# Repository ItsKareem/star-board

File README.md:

# A star-shaped blinky board ݁˖ .☆

An LED chaser PCB that uses a NE555 timer (astable mode) and a CD4017 decade counter. I designed the PCB in the shape of a star and added custom silkscreen art to make it more personal. This makes a really cute desk toy and just a fun/beginner-friendly elecronics project. 

## Features
- LED chasing animation with 10 LEDs
- Animation speed can be adjusted using a potentiometer
- Custom star-shaped PCB outline
- Silkscreen art made by me
- THT components

Basically, the 555 generates clock pulses which fed into the CD4017, which sequentially activates each LED, creating the chasing animation.

I made this project as a qualifying project for [fallout](https://www.fallout.hackclub.com), a hardware hackathon organized by hack club Shenzhen, China.

### Front:

### Back:

### PCB:

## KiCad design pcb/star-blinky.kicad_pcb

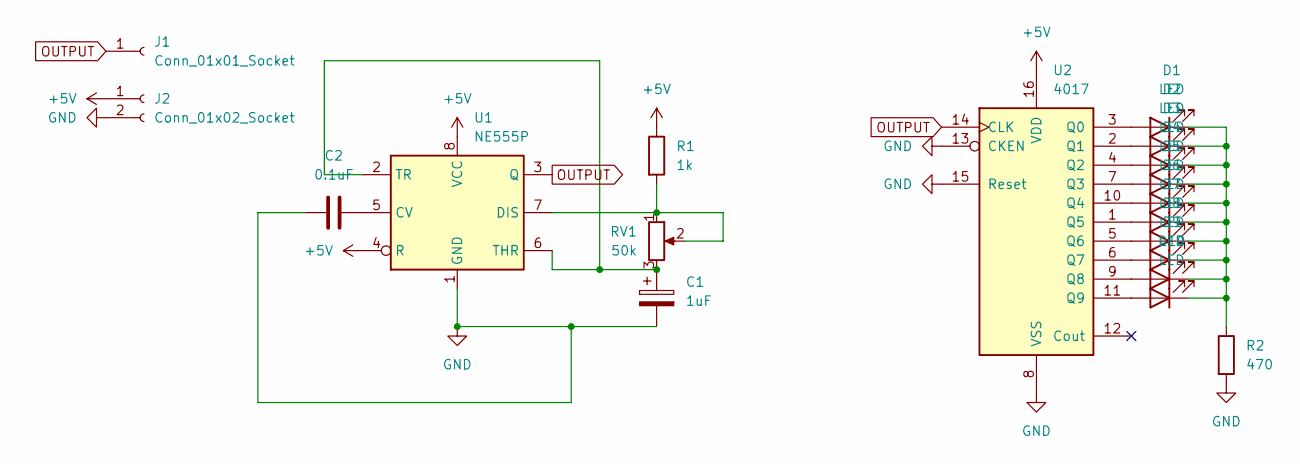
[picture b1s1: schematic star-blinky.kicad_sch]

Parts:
C1: 1uF; CP_Radial_D5.0mm_P2.00mm
C2: 0.1uF; C_Disc_D7.5mm_W2.5mm_P5.00mm
D1, D2, D3, D4, D5, D6, D7, D8, D9, D10: LED; LED_D3.0mm
J1: Conn_01x01_Socket; PinHeader_1x01_P2.54mm_Vertical
J2: Conn_01x02_Socket; PinHeader_1x02_P2.54mm_Vertical
R1: 1k; R_Axial_DIN0207_L6.3mm_D2.5mm_P7.62mm_Horizontal
R2: 470; R_Axial_DIN0207_L6.3mm_D2.5mm_P7.62mm_Horizontal
RV1: 50k; Potentiometer_Vishay_T93YA_Vertical
U1: NE555P; DIP-8_W7.62mm
U2: 4017; N16

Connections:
+5V: J2.1, R1.1, U1.4 (R), U1.8 (VCC), U2.16 (VDD)
GND: C1.2, C2.2, J2.2, R2.2, U1.1 (GND), U2.8 (VSS), U2.13 (CKEN), U2.15 (Reset)
unnamed: D1.2 (A), U2.3 (Q0)
unnamed: D1.1 (K), D2.1 (K), D3.1 (K), D4.1 (K), D5.1 (K), D6.1 (K), D7.1 (K), D8.1 (K), D9.1 (K), D10.1 (K), R2.1
unnamed: D2.2 (A), U2.2 (Q1)
unnamed: D3.2 (A), U2.4 (Q2)
unnamed: D4.2 (A), U2.7 (Q3)
unnamed: D5.2 (A), U2.10 (Q4)
unnamed: D6.2 (A), U2.1 (Q5)
unnamed: D7.2 (A), U2.5 (Q6)
unnamed: D8.2 (A), U2.6 (Q7)
unnamed: D9.2 (A), U2.9 (Q8)
unnamed: D10.2 (A), U2.11 (Q9)
unnamed: C2.1, U1.5 (CV)
unnamed: R1.2, RV1.1, RV1.2, U1.7 (DIS)
unnamed: C1.1, RV1.3, U1.2 (TR), U1.6 (THR)
OUTPUT: J1.1, U1.3 (Q), U2.14 (CLK)

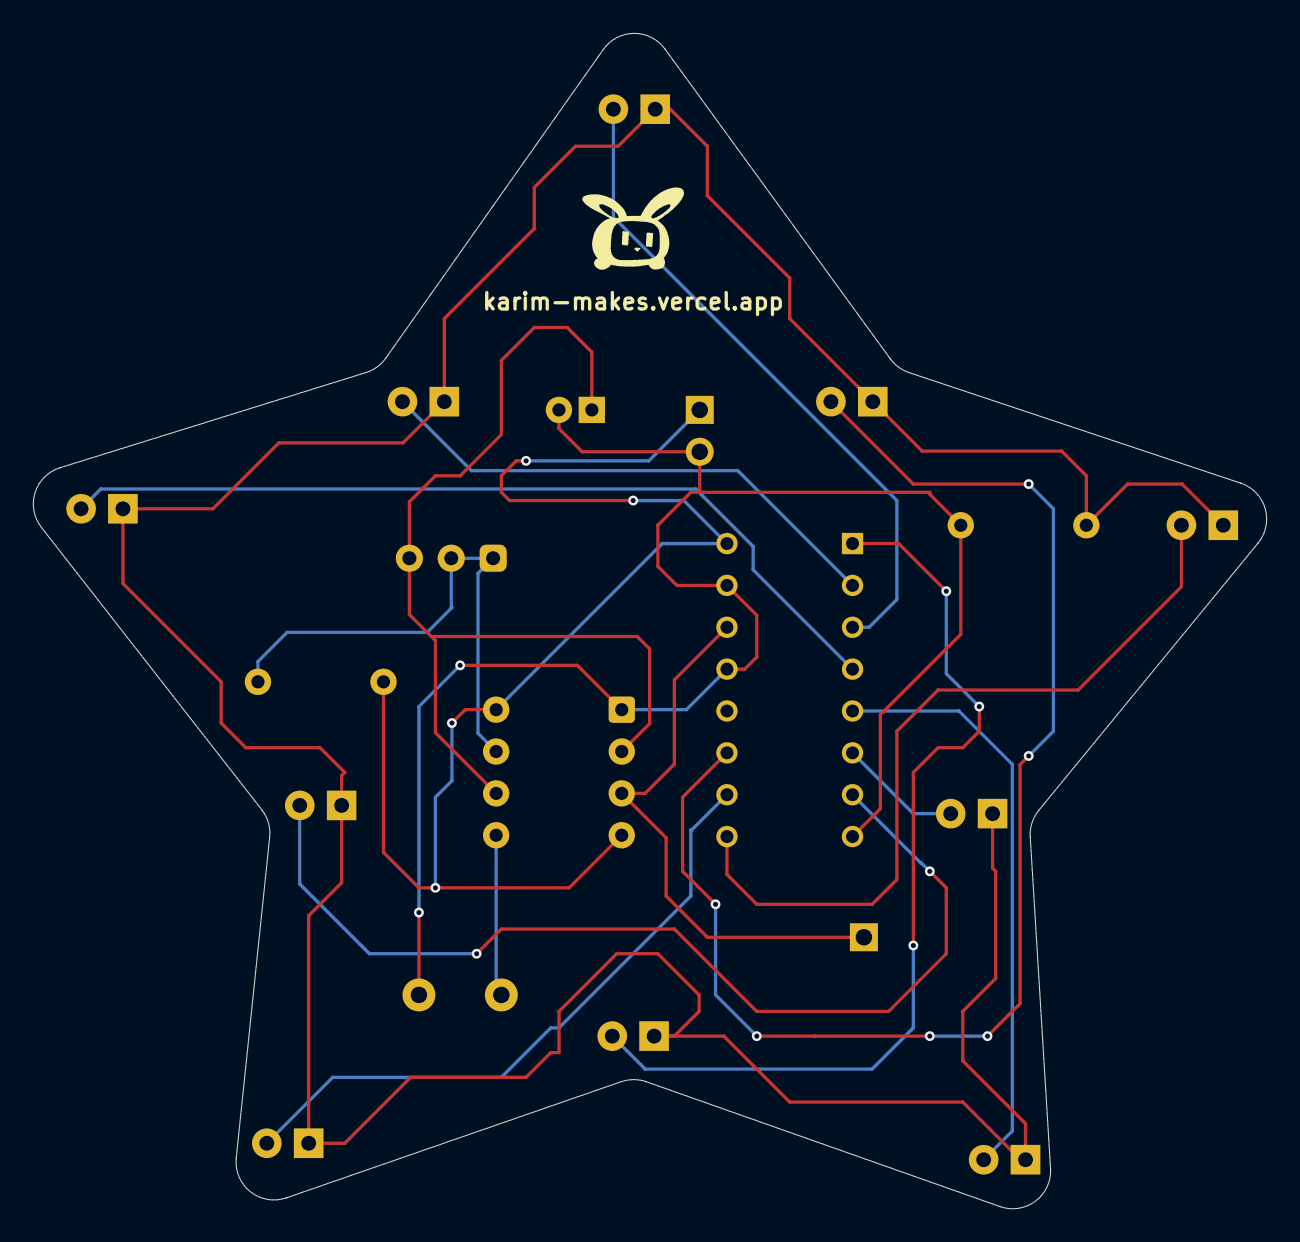
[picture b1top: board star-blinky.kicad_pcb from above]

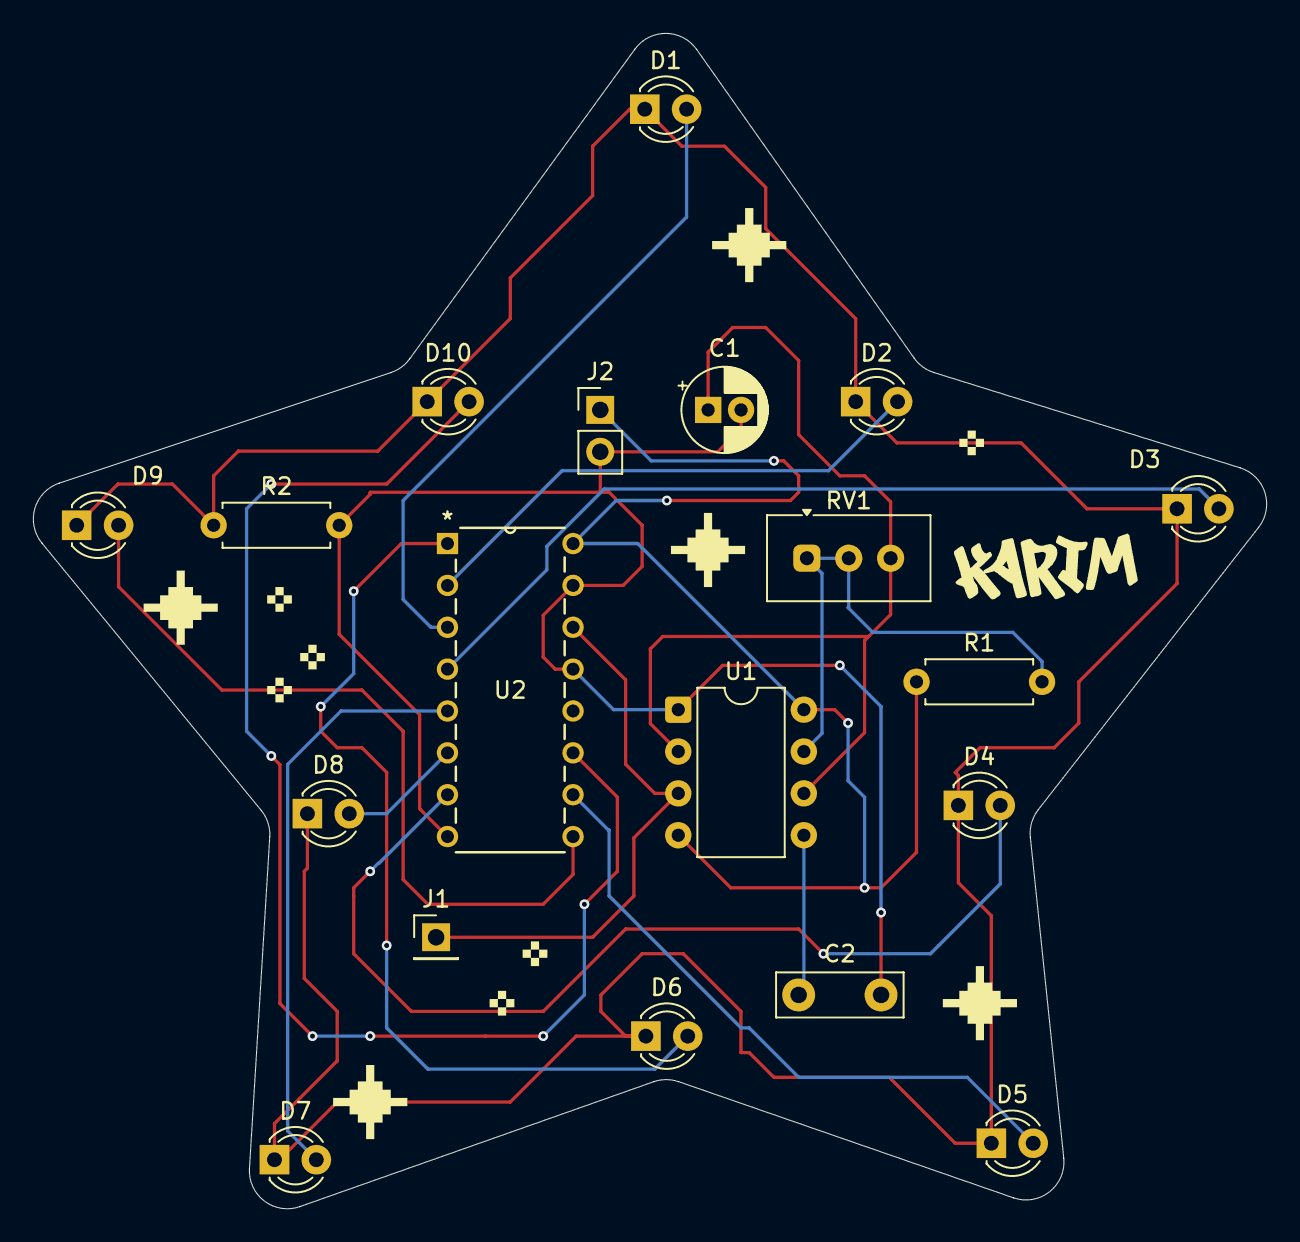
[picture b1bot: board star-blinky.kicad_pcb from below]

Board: 2 copper layers, 74.8 x 71.3 mm, 19 parts (19 on the bottom side), 17 nets.

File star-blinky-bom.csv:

Reference,Qty,Cost (EGP),Value,Footprint,Datasheet
C1,1,0.6,1uF,Capacitor_THT:CP_Radial_D5.0mm_P2.00mm,~
C2,1,1,0.1uF,Capacitor_THT:C_Disc_D7.5mm_W2.5mm_P5.00mm,~
"D1,D2,D3,D4,D5,D6,D7,D8,D9,D10",10,5,LED,LED_THT:LED_D3.0mm,~
J1,1,1.25,Conn_01x01_Socket,Connector_PinHeader_2.54mm:PinHeader_1x01_P2.54mm_Vertical,~
J2,1,1.25,Conn_01x02_Socket,Connector_PinHeader_2.54mm:PinHeader_1x02_P2.54mm_Vertical,~
R1,1,0.25,1k,Resistor_THT:R_Axial_DIN0207_L6.3mm_D2.5mm_P7.62mm_Horizontal,~
R2,1,0.25,470,Resistor_THT:R_Axial_DIN0207_L6.3mm_D2.5mm_P7.62mm_Horizontal,~
RV1,1,6,50k,Potentiometer_THT:Potentiometer_Vishay_T93YA_Vertical,~
U1,1,10,NE555P,Package_DIP:DIP-8_W7.62mm,http://www.ti.com/lit/ds/symlink/ne555.pdf
U2,1,15,4017,custom:N16,http://www.intersil.com/content/dam/Intersil/documents/cd40/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
Total,,40.6,,,

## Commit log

2026-06-20 Rename project from 'star-blinky' to 'star-board'
2026-06-20 Improved the README
    Updated README to include project details, features, and images.
2026-06-20 Uploaded relevant KiCad files
2026-06-20 Uploaded Images and BOM
2026-06-20 Added images into a folder and added the zine page
2026-06-20 organized ts
2026-06-20 Fix image links and add schematic section in README
    Updated image sources in README and added schematic section.
2026-06-20 README edits
2026-06-23 Review Team Edit: Add Zine Page as Image
2026-06-23 Review Team Edit: Added Zine Page to README
